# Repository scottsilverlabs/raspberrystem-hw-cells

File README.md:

raspberrystem-hw-cells
======================

raspberrySTEM(TM) Cells hardware schematics and related documents

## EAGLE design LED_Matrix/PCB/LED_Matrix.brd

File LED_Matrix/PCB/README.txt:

File List

gerbers/*.GBL       Bottom Copper
gerbers/*.GBO       Bottom Silkscreen
gerbers/*.GBS       Bottom Soldermask
gerbers/*.GTL       Top Copper
gerbers/*.GTO       Top Silkscreen
gerbers/*.GTP       Top Paste
gerbers/*.GTS       Top Soldermask
gerbers/*.TXT       Drill File
gerbers/*.dri       Drill Station Info File
gerbers/*.gpi       Photoplotter Info File   
*.brd               EagleCAD Board File
*.lbr               EagleCAD Library File
*.sch               EagleCAD Schematic File
*_BOM.xls           BOM
README.txt          This file
*.jpg               Reference images

Notes:

- Gerber Files Generated from EagleCAD 7.1 CAM Processor using sfe-gerb274x.cam
  from www.sparkfun.com
- All parts and assembly should be Lead-Free RoHS compliant

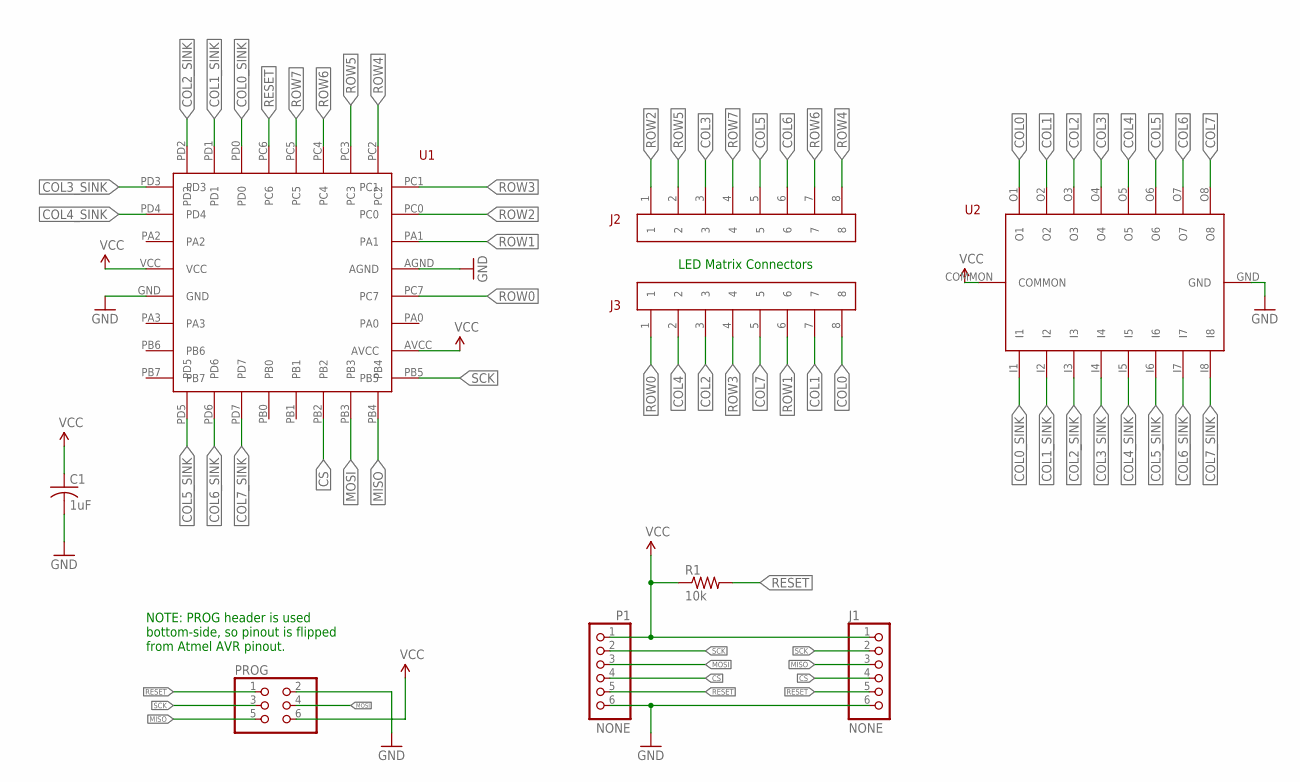
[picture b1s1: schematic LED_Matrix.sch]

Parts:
C1: 1uF; C0603
J1: NONE; 1X06
J2, J3: HEADER-1X8
P1: NONE; 1X06
PROG: NONE; 2X03
R1: 10k; R0603
U1: ATTINY48
U2: ULN2803AFWG

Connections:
COL0: J3.8, U2.O1
COL0_SINK: U1.PD0, U2.I1
COL1: J3.7, U2.O2
COL1_SINK: U1.PD1, U2.I2
COL2: J3.3, U2.O3
COL2_SINK: U1.PD2, U2.I3
COL3: J2.3, U2.O4
COL3_SINK: U1.PD3, U2.I4
COL4: J3.2, U2.O5
COL4_SINK: U1.PD4, U2.I5
COL5: J2.5, U2.O6
COL5_SINK: U1.PD5, U2.I6
COL6: J2.6, U2.O7
COL6_SINK: U1.PD6, U2.I7
COL7: J3.5, U2.O8
COL7_SINK: U1.PD7, U2.I8
CS: J1.4, P1.4, U1.PB2
GND: C1.2, J1.6, P1.6, PROG.2, U1.AGND, U1.GND, U2.GND
MISO: J1.3, PROG.5, U1.PB4
MOSI: P1.3, PROG.4, U1.PB3
RESET: J1.5, P1.5, PROG.1, R1.2, U1.PC6
ROW0: J3.1, U1.PC7
ROW1: J3.6, U1.PA1
ROW2: J2.1, U1.PC0
ROW3: J3.4, U1.PC1
ROW4: J2.8, U1.PC2
ROW5: J2.2, U1.PC3
ROW6: J2.7, U1.PC4
ROW7: J2.4, U1.PC5
SCK: J1.2, P1.2, PROG.3, U1.PB5
VCC: C1.1, J1.1, P1.1, PROG.6, R1.1, U1.AVCC, U1.VCC, U2.COMMON

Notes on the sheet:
NOTE: PROG header is used bottom-side, so pinout is flipped from Atmel AVR pinout.
LED Matrix Connectors

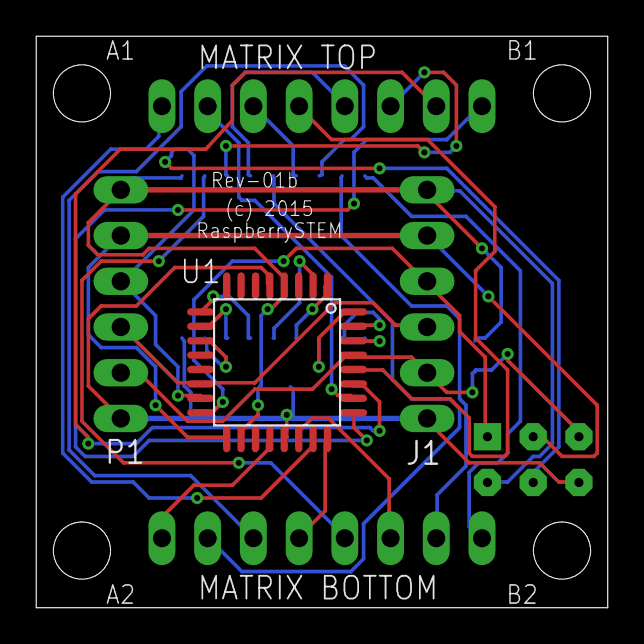
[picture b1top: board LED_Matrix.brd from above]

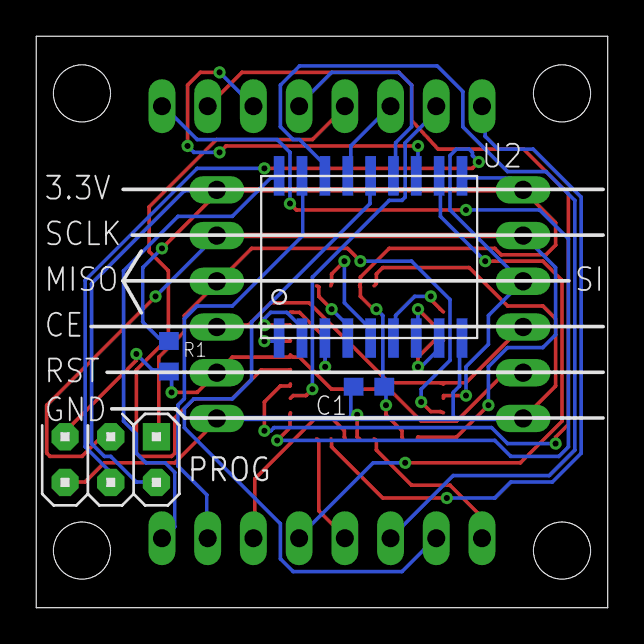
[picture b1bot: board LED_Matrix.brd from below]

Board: 2 copper layers, 31.8 x 31.8 mm, 9 parts (3 on the bottom side), 31 nets.

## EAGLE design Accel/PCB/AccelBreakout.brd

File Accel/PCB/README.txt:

File List

gerbers/*.GBL       Bottom Copper
gerbers/*.GBO       Bottom Silkscreen
gerbers/*.GBS       Bottom Soldermask
gerbers/*.GTL       Top Copper
gerbers/*.GTO       Top Silkscreen
gerbers/*.GTP       Top Paste
gerbers/*.GTS       Top Soldermask
gerbers/*.TXT       Drill File
gerbers/*.dri       Drill Station Info File
gerbers/*.gpi       Photoplotter Info File   
*.brd               EagleCAD Board File
*.lbr               EagleCAD Library File
*.sch               EagleCAD Schematic File
*_BOM.xls           BOM
README.txt          This file
*.jpg               Reference images

Notes:

- Gerber Files Generated from EagleCAD 7.1 CAM Processor using sfe-gerb274x.cam
  from www.sparkfun.com
- All parts and assembly should be Lead-Free RoHS compliant
- Refer to the JPG images for through-hole part orientation.

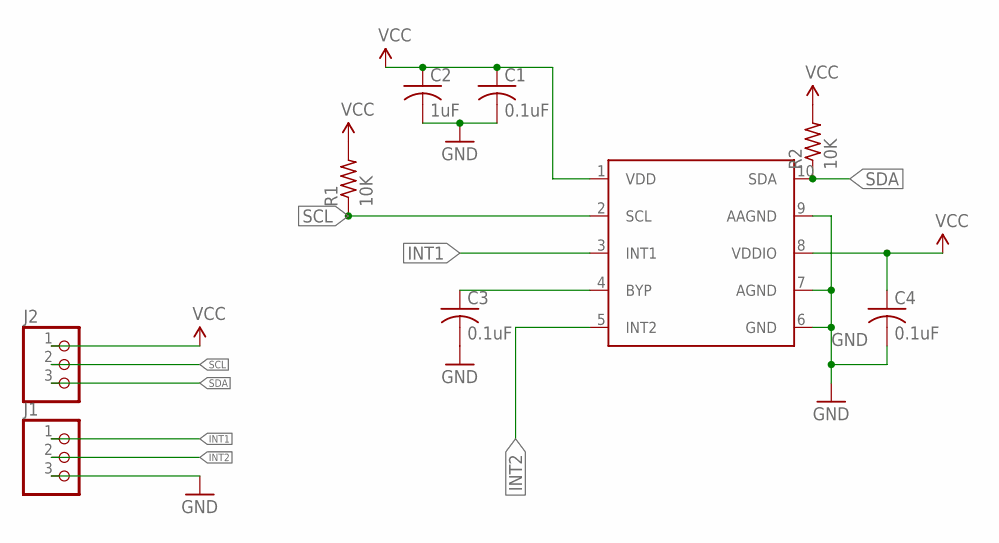
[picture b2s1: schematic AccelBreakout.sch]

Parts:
C1, C3, C4: 0.1uF; C0603
C2: 1uF; C0603
J1, J2: PINHD-1X3; 1X03
R1, R2: 10K; R0603
U1: MMA8653FCR1

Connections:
GND: C1.2, C2.2, C3.2, C4.2, J1.3, U1.6 (GND), U1.7 (AGND), U1.9 (AAGND)
INT1: J1.1, U1.3 (INT1)
INT2: J1.2, U1.5 (INT2)
unnamed: C3.1, U1.4 (BYP)
SCL: J2.2, R1.1, U1.2 (SCL)
SDA: J2.3, R2.1, U1.10 (SDA)
VCC: C1.1, C2.1, C4.1, J2.1, R1.2, R2.2, U1.1 (VDD), U1.8 (VDDIO)

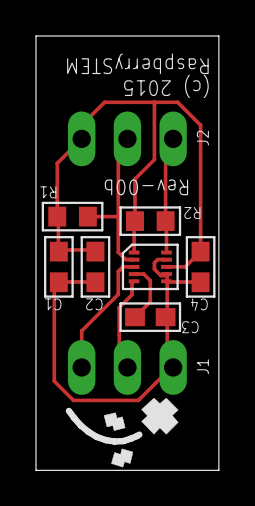
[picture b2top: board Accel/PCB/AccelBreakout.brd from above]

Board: 2 copper layers, 10.2 x 24.1 mm, 9 parts (0 on the bottom side), 7 nets.

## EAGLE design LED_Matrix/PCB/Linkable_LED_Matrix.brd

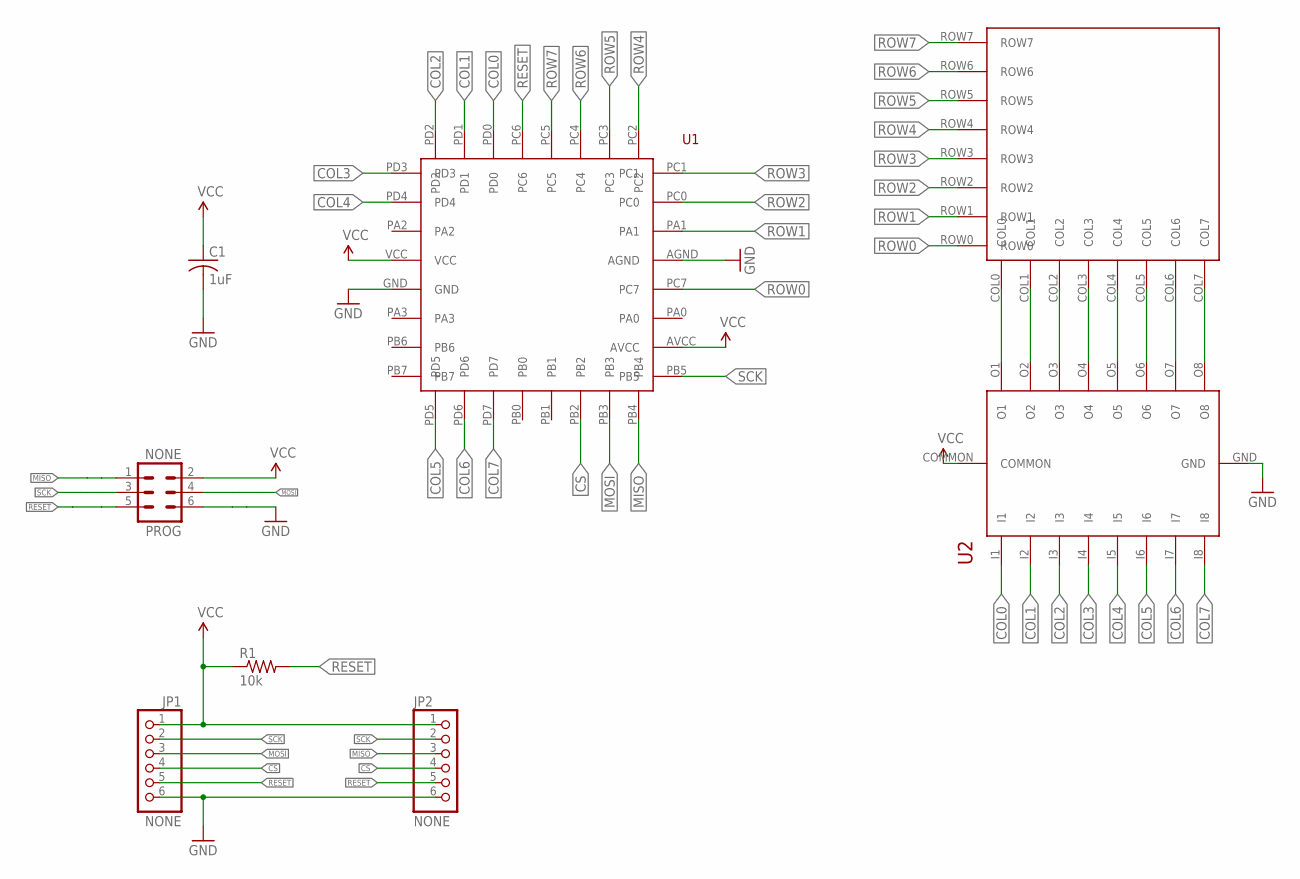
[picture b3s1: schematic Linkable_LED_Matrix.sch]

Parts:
C1: 1uF; C0603
JP1, JP2: NONE; 1X06
LEDMATRIX: 8X8_LED_MATRIX
PROG: NONE; MA03-2
R1: 10k; R0603
U1: ATTINY48
U2: ULN2803AFWG

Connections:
COL0: U1.PD0, U2.I1
COL1: U1.PD1, U2.I2
COL2: U1.PD2, U2.I3
COL3: U1.PD3, U2.I4
COL4: U1.PD4, U2.I5
COL5: U1.PD5, U2.I6
COL6: U1.PD6, U2.I7
COL7: U1.PD7, U2.I8
CS: JP1.4, JP2.4, U1.PB2
GND: C1.2, JP1.6, JP2.6, PROG.6, U1.AGND, U1.GND, U2.GND
MISO: JP2.3, PROG.1, U1.PB4
MOSI: JP1.3, PROG.4, U1.PB3
unnamed: LEDMATRIX.COL0, U2.O1
unnamed: LEDMATRIX.COL1, U2.O2
unnamed: LEDMATRIX.COL2, U2.O3
unnamed: LEDMATRIX.COL3, U2.O4
unnamed: LEDMATRIX.COL4, U2.O5
unnamed: LEDMATRIX.COL5, U2.O6
unnamed: LEDMATRIX.COL6, U2.O7
unnamed: LEDMATRIX.COL7, U2.O8
RESET: JP1.5, JP2.5, PROG.5, R1.2, U1.PC6
ROW0: LEDMATRIX.ROW0, U1.PC7
ROW1: LEDMATRIX.ROW1, U1.PA1
ROW2: LEDMATRIX.ROW2, U1.PC0
ROW3: LEDMATRIX.ROW3, U1.PC1
ROW4: LEDMATRIX.ROW4, U1.PC2
ROW5: LEDMATRIX.ROW5, U1.PC3
ROW6: LEDMATRIX.ROW6, U1.PC4
ROW7: LEDMATRIX.ROW7, U1.PC5
SCK: JP1.2, JP2.2, PROG.3, U1.PB5
VCC: C1.1, JP1.1, JP2.1, PROG.2, R1.1, U1.AVCC, U1.VCC, U2.COMMON

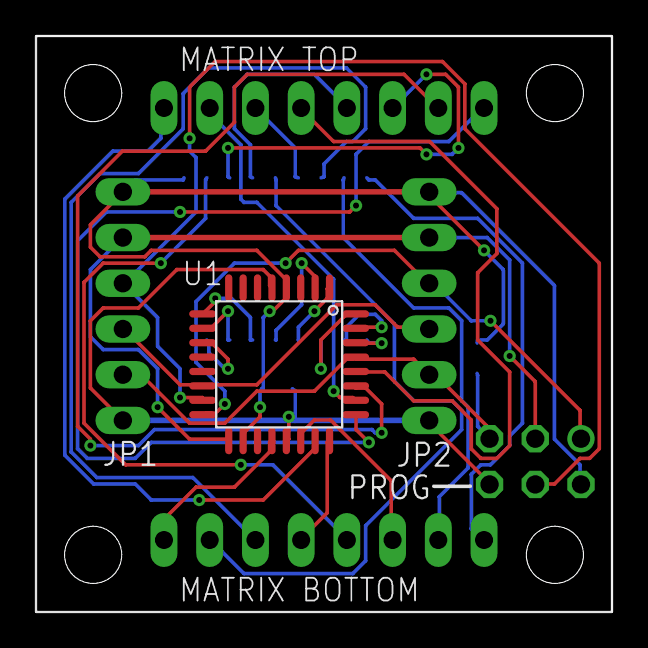
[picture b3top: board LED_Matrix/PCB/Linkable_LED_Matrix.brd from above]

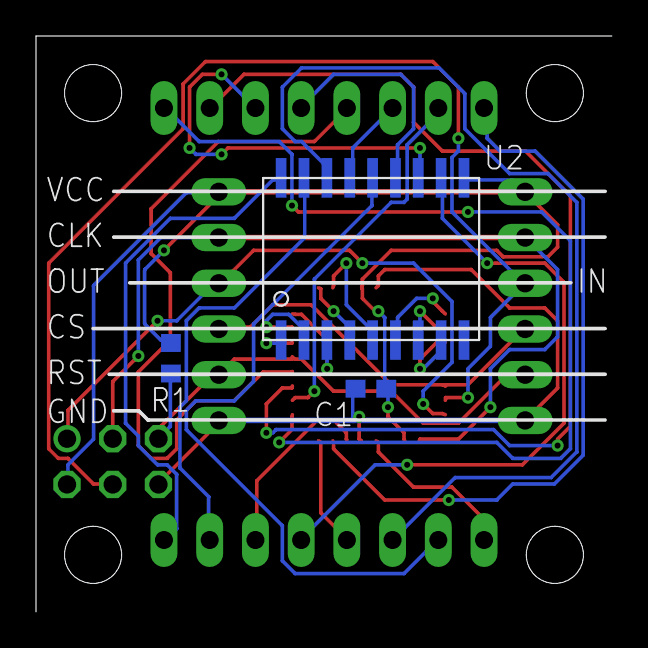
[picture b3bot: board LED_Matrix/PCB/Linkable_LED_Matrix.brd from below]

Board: 2 copper layers, 32.0 x 32.0 mm, 8 parts (3 on the bottom side), 31 nets.

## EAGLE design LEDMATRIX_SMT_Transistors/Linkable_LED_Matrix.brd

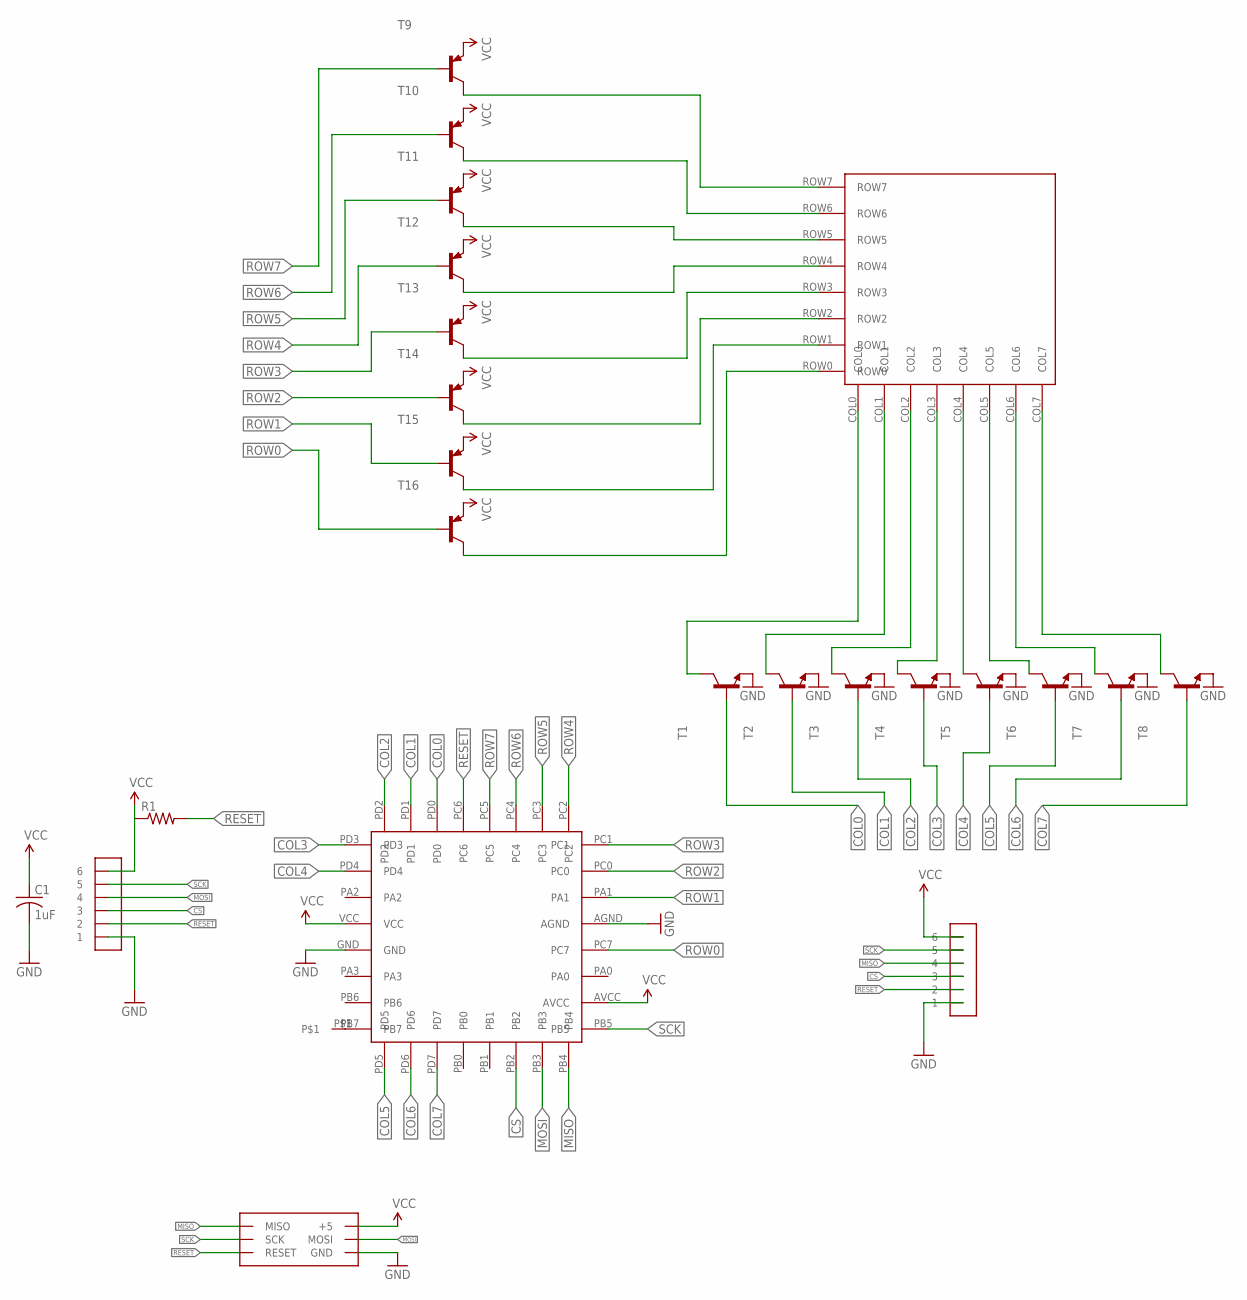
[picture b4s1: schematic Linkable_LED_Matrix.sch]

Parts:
C1: 1uF; C0603
R1: R-US_R0603; R0603
T1, T2, T3, T4, T5, T6, T7, T8: MMBT2222ALT1-NPN-SOT23-BEC; SOT23-BEC
T9, T10, T11, T12, T13, T14, T15, T16: MMBT3906LT1-PNP-SOT23-BEC; SOT23-BEC
U$1: ATTINY48
U$3: 8X8_LED_MATRIX
U$5: 1X1MM_PAD
U$6, U$7: DIP1X6MALE
U$9: DIP2X3MALE

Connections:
COL0: T1.B, U$1.PD0
COL1: T2.B, U$1.PD1
COL2: T3.B, U$1.PD2
COL3: T4.B, U$1.PD3
COL4: T5.B, U$1.PD4
COL5: T6.B, U$1.PD5
COL6: T7.B, U$1.PD6
COL7: T8.B, U$1.PD7
CS: U$1.PB2, U$6.3, U$7.3
GND: C1.2, T1.E, T2.E, T3.E, T4.E, T5.E, T6.E, T7.E, T8.E, U$1.AGND, U$1.GND, U$6.1, U$7.1, U$9.GND
MISO: U$1.PB4, U$7.4, U$9.MISO
MOSI: U$1.PB3, U$6.4, U$9.MOSI
unnamed: T1.C, U$3.COL0
unnamed: T3.C, U$3.COL2
unnamed: T4.C, U$3.COL3
unnamed: T5.C, U$3.COL4
unnamed: T6.C, U$3.COL5
unnamed: T7.C, U$3.COL6
unnamed: T8.C, U$3.COL7
unnamed: U$1.PB7, U$5.P$1
unnamed: T2.C, U$3.COL1
unnamed: T9.C, U$3.ROW7
unnamed: T10.C, U$3.ROW6
unnamed: T11.C, U$3.ROW5
unnamed: T12.C, U$3.ROW4
unnamed: T13.C, U$3.ROW3
unnamed: T14.C, U$3.ROW2
unnamed: T15.C, U$3.ROW1
unnamed: T16.C, U$3.ROW0
RESET: R1.2, U$1.PC6, U$6.2, U$7.2, U$9.RESET
ROW0: T16.B, U$1.PC7
ROW1: T15.B, U$1.PA1
ROW2: T14.B, U$1.PC0
ROW3: T13.B, U$1.PC1
ROW4: T12.B, U$1.PC2
ROW5: T11.B, U$1.PC3
ROW6: T10.B, U$1.PC4
ROW7: T9.B, U$1.PC5
SCK: U$1.PB5, U$6.5, U$7.5, U$9.SCK
VCC: C1.1, R1.1, T9.E, T10.E, T11.E, T12.E, T13.E, T14.E, T15.E, T16.E, U$1.AVCC, U$1.VCC, U$6.6, U$7.6, U$9.5V (+5)

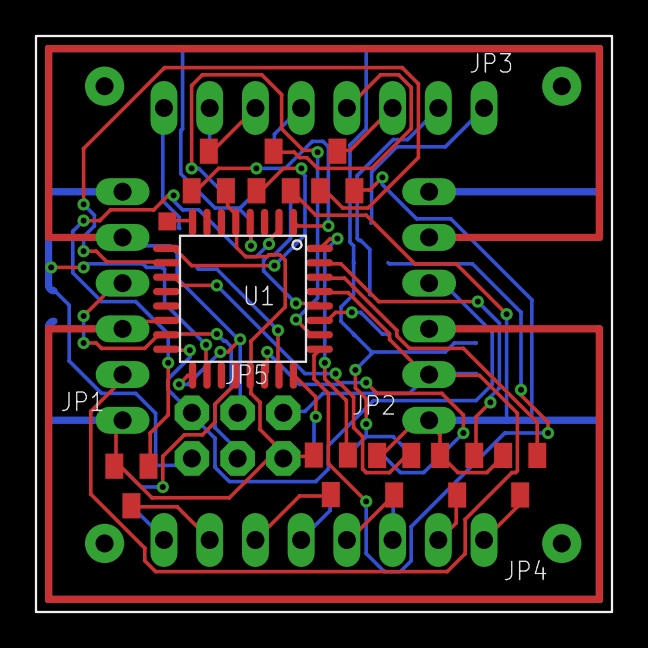
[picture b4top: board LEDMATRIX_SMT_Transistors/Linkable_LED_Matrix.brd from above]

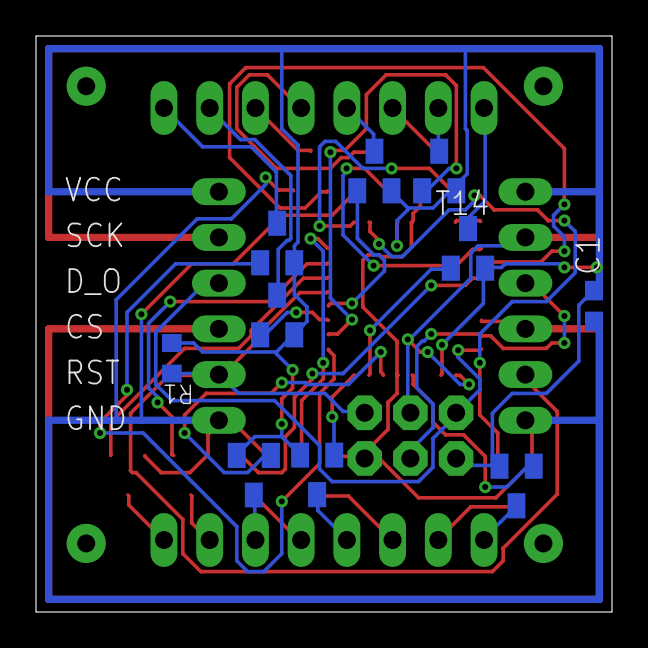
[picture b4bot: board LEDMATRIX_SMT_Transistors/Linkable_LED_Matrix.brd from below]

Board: 2 copper layers, 32.0 x 32.0 mm, 24 parts (11 on the bottom side), 40 nets.

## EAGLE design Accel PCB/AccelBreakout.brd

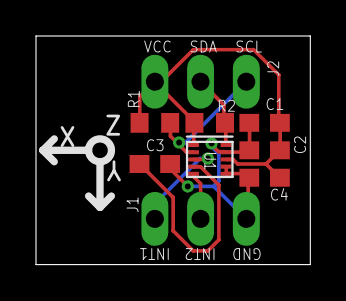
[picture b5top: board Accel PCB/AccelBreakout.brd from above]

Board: 2 copper layers, 15.2 x 12.7 mm, 10 parts (0 on the bottom side), 7 nets.

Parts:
C1, C3, C4: 0.1uF; C0603
C2: 1uF; C0603
R1, R2: 10K; R0603
U$2: ACCELDIR
U$3, U$4: DIP1X3MALE
U$23: MMA8653FCR1

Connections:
GND: C1.2, C2.2, C3.2, C4.2, U$4.P$3, U$23.6, U$23.7, U$23.9
INT1: U$4.P$1, U$23.3
INT2: U$4.P$2, U$23.5
unnamed: C3.1, U$23.4
SCL: R1.1, U$3.P$3, U$23.2
SDA: R2.1, U$3.P$2, U$23.10
VCC: C1.1, C2.1, C4.1, R1.2, R2.2, U$3.P$1, U$23.1, U$23.8

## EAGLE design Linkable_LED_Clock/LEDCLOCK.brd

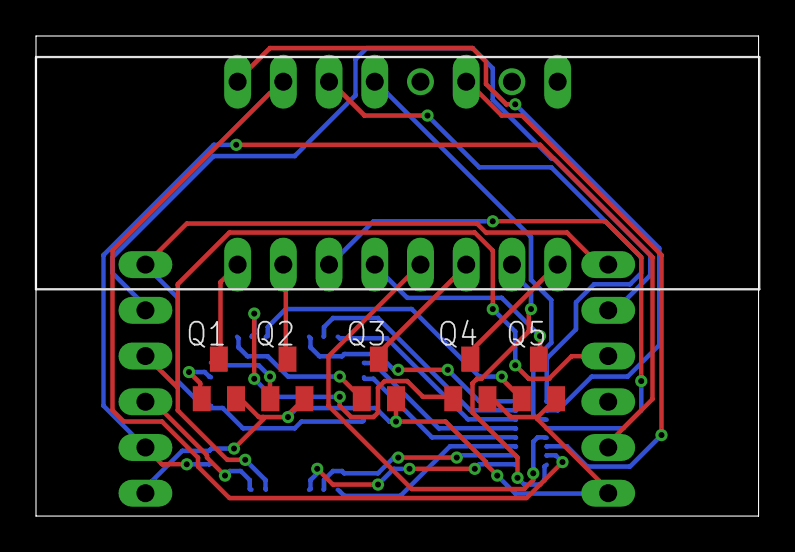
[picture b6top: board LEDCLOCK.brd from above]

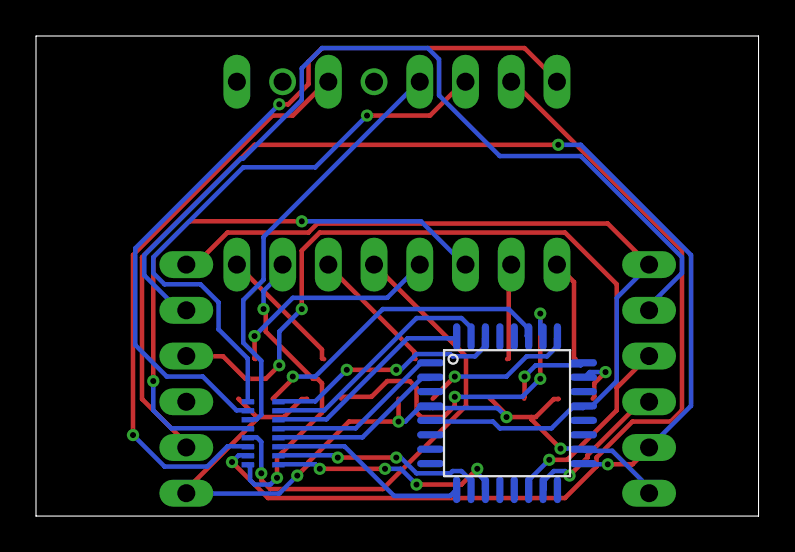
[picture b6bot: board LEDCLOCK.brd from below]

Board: 2 copper layers, 40.1 x 26.7 mm, 10 parts (2 on the bottom side), 32 nets.

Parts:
Q1, Q2, Q3, Q4, Q5: MMBT2907ALT1SMD; SOT23-BEC
U$1: LEDCLOCK
U$2, U$4: DIP1X6MALE
U$3: RES_ARRAY
U$5: ATTINY48

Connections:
A: U$3.R8, U$5.PD0
B: U$3.R7, U$5.PD1
C: U$3.R6, U$5.PD2
CLK: U$2.2, U$4.2, U$5.PB5
D: U$3.R5, U$5.PD3
DIGIT1: Q1.B, U$5.PC0
DIGIT2: Q2.B, U$5.PC1
DIGIT3: Q3.B, U$5.PC2
DIGIT4: Q4.B, U$5.PC3
DP: U$3.R1, U$5.PD7
E: U$3.R4, U$5.PD4
F: U$3.R3, U$5.PD5
G: U$3.R2, U$5.PD6
GND: U$2.6, U$4.6, U$5.AGND, U$5.GND
MOD: Q5.B, U$5.PC4
MOSI: U$2.3, U$5.PB3
unnamed: Q1.C, U$1.1
unnamed: Q2.C, U$1.2
unnamed: Q3.C, U$1.6
unnamed: Q4.C, U$1.8
unnamed: Q5.C, U$1.4
RA: U$1.14, U$3.8R
RB: U$1.16, U$3.7R
RC: U$1.13, U$3.6R
RD: U$1.3, U$3.5R
RDP: U$1.7, U$3.1R
RE: U$1.5, U$3.4R
RESET: U$2.5, U$4.5
RF: U$1.11, U$3.3R
RG: U$1.15, U$3.2R
SS: U$2.4, U$4.4, U$5.PB2
VCC: Q1.E, Q2.E, Q3.E, Q4.E, Q5.E, U$2.1, U$4.1, U$5.AVCC, U$5.VCC

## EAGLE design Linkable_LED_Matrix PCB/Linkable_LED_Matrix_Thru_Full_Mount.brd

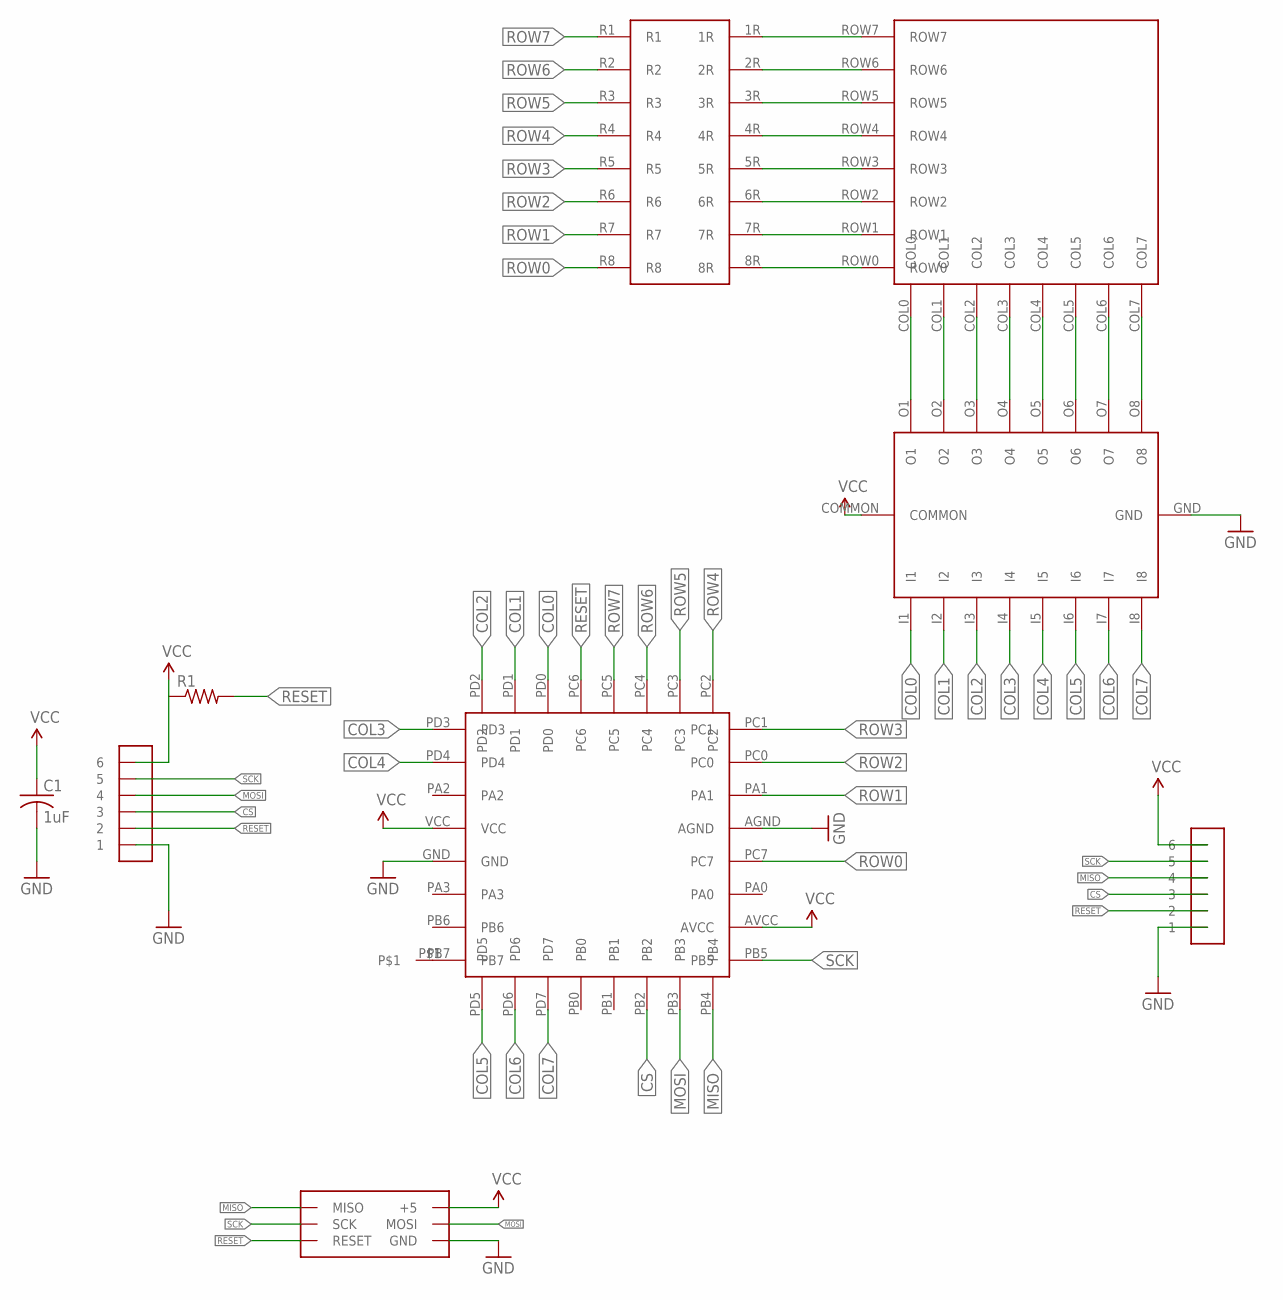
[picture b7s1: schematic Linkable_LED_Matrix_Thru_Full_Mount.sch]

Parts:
C1: 1uF; C0603
R1: R-US_R0603; R0603
U$1: ATTINY48
U$2: ULN2803AFWG
U$3: 8X8_LED_MATRIX
U$4: RES_ARRAY
U$5: 1X1MM_PAD
U$6, U$7: DIP1X6MALE
U$9: DIP2X3MALE

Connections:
COL0: U$1.PD0, U$2.I1
COL1: U$1.PD1, U$2.I2
COL2: U$1.PD2, U$2.I3
COL3: U$1.PD3, U$2.I4
COL4: U$1.PD4, U$2.I5
COL5: U$1.PD5, U$2.I6
COL6: U$1.PD6, U$2.I7
COL7: U$1.PD7, U$2.I8
CS: U$1.PB2, U$6.3, U$7.3
GND: C1.2, U$1.AGND, U$1.GND, U$2.GND, U$6.1, U$7.1, U$9.GND
MISO: U$1.PB4, U$7.4, U$9.MISO
MOSI: U$1.PB3, U$6.4, U$9.MOSI
unnamed: U$2.O1, U$3.COL0
unnamed: U$2.O2, U$3.COL1
unnamed: U$2.O3, U$3.COL2
unnamed: U$2.O4, U$3.COL3
unnamed: U$2.O5, U$3.COL4
unnamed: U$2.O6, U$3.COL5
unnamed: U$2.O7, U$3.COL6
unnamed: U$2.O8, U$3.COL7
unnamed: U$1.PB7, U$5.P$1
unnamed: U$3.ROW7, U$4.1R
unnamed: U$3.ROW6, U$4.2R
unnamed: U$3.ROW5, U$4.3R
unnamed: U$3.ROW4, U$4.4R
unnamed: U$3.ROW3, U$4.5R
unnamed: U$3.ROW2, U$4.6R
unnamed: U$3.ROW1, U$4.7R
unnamed: U$3.ROW0, U$4.8R
RESET: R1.2, U$1.PC6, U$6.2, U$7.2, U$9.RESET
ROW0: U$1.PC7, U$4.R8
ROW1: U$1.PA1, U$4.R7
ROW2: U$1.PC0, U$4.R6
ROW3: U$1.PC1, U$4.R5
ROW4: U$1.PC2, U$4.R4
ROW5: U$1.PC3, U$4.R3
ROW6: U$1.PC4, U$4.R2
ROW7: U$1.PC5, U$4.R1
SCK: U$1.PB5, U$6.5, U$7.5, U$9.SCK
VCC: C1.1, R1.1, U$1.AVCC, U$1.VCC, U$2.COMMON, U$6.6, U$7.6, U$9.5V (+5)

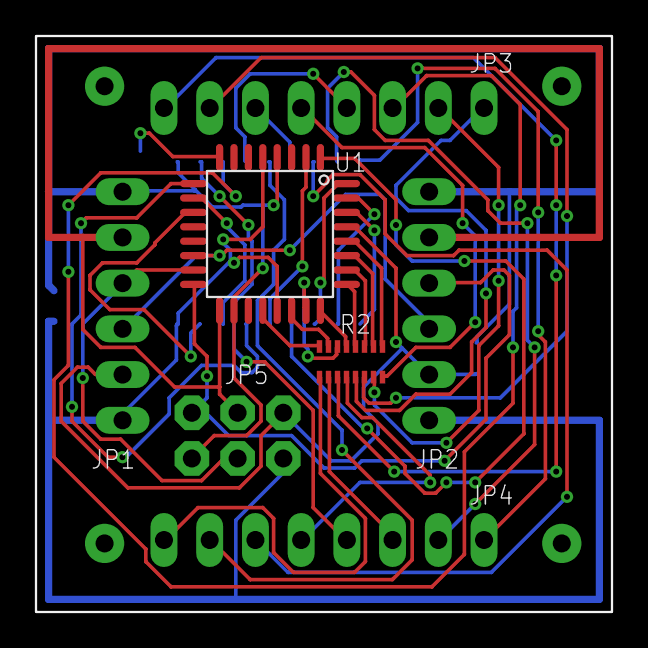
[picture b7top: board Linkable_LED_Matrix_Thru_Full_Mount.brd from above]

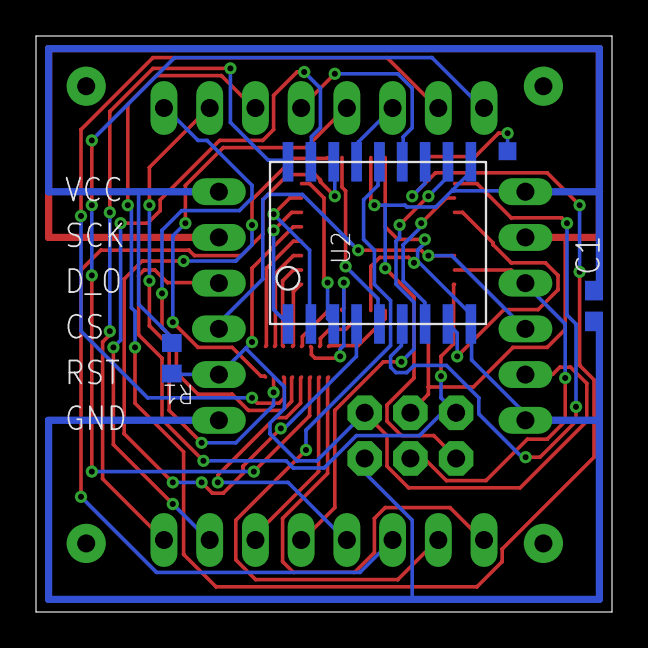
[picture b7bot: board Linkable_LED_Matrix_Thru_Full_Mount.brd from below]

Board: 2 copper layers, 32.0 x 32.0 mm, 10 parts (5 on the bottom side), 40 nets.

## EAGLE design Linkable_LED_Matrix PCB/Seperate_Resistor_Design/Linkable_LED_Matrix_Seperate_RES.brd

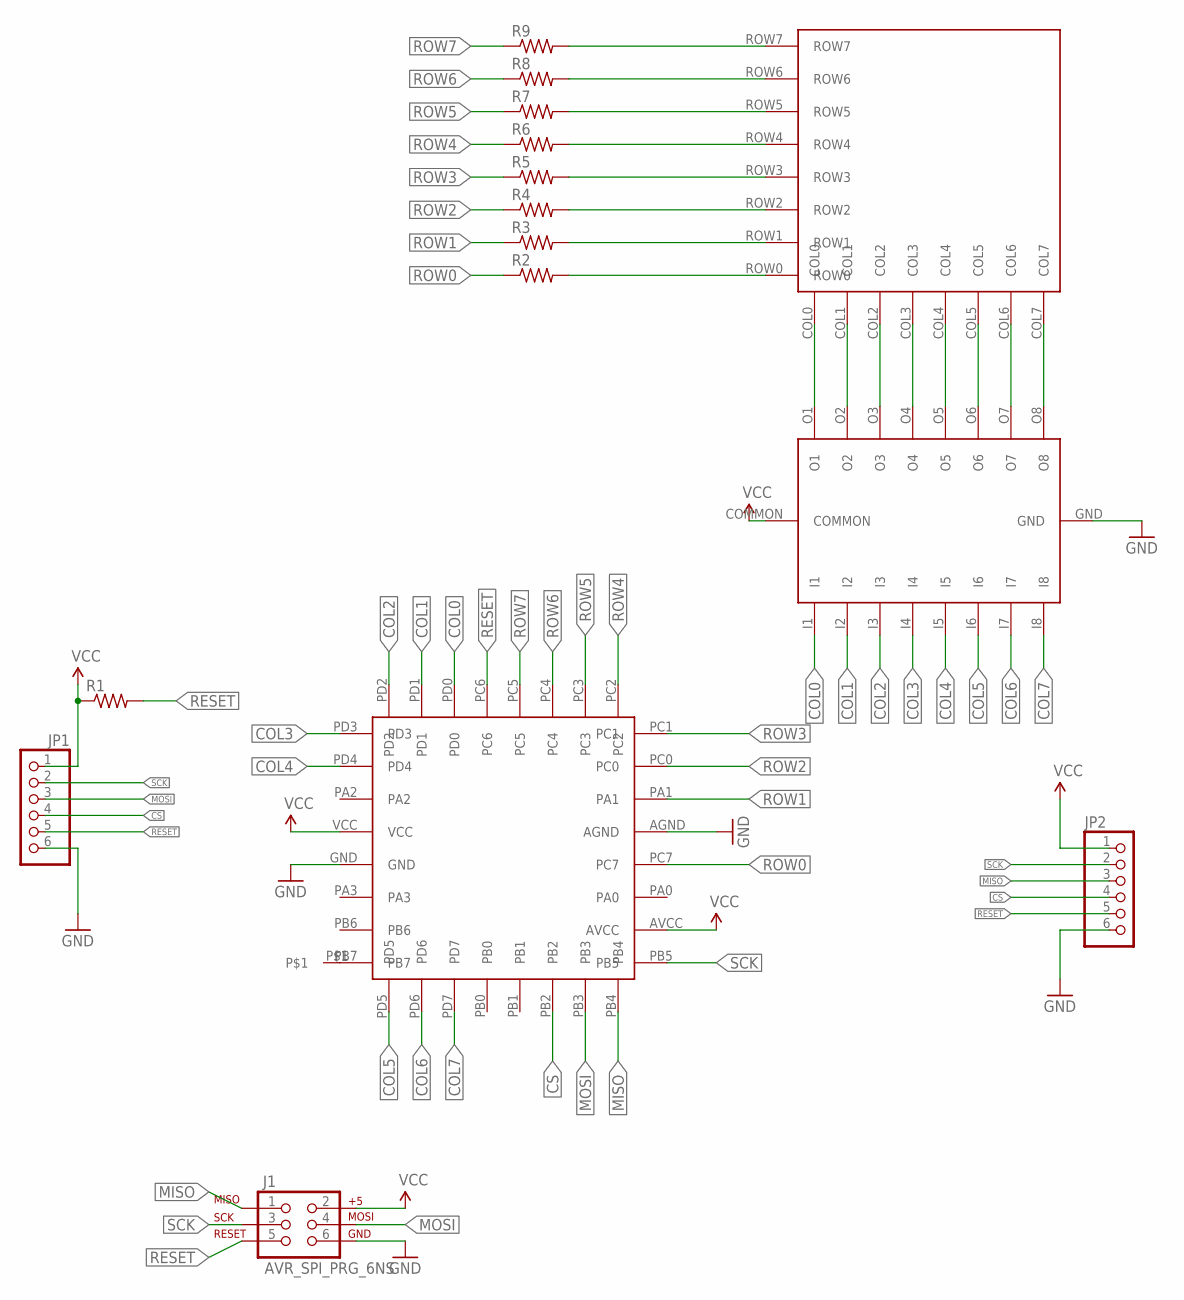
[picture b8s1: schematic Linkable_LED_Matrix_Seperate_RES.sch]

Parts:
J1: AVR_SPI_PRG_6NS; 2X3-NS
JP1, JP2: PINHD-1X6; 1X06
R1, R2, R3, R4, R5, R6, R7, R8, R9: R-US_R0603; R0603
U$1: ATTINY48
U$2: ULN2803AFWG
U$3: 8X8_LED_MATRIX
U$4: 1X1MM_PAD

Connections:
COL0: U$1.PD0, U$2.I1
COL1: U$1.PD1, U$2.I2
COL2: U$1.PD2, U$2.I3
COL3: U$1.PD3, U$2.I4
COL4: U$1.PD4, U$2.I5
COL5: U$1.PD5, U$2.I6
COL6: U$1.PD6, U$2.I7
COL7: U$1.PD7, U$2.I8
CS: JP1.4, JP2.4, U$1.PB2
GND: J1.6, JP1.6, JP2.6, U$1.AGND, U$1.GND, U$2.GND
MISO: J1.1, JP2.3, U$1.PB4
MOSI: J1.4, JP1.3, U$1.PB3
unnamed: U$2.O1, U$3.COL0
unnamed: U$2.O2, U$3.COL1
unnamed: U$2.O3, U$3.COL2
unnamed: U$2.O4, U$3.COL3
unnamed: U$2.O5, U$3.COL4
unnamed: U$2.O6, U$3.COL5
unnamed: U$2.O7, U$3.COL6
unnamed: U$2.O8, U$3.COL7
unnamed: U$1.PB7, U$4.P$1
unnamed: R9.2, U$3.ROW7
unnamed: R8.2, U$3.ROW6
unnamed: R7.2, U$3.ROW5
unnamed: R6.2, U$3.ROW4
unnamed: R5.2, U$3.ROW3
unnamed: R4.2, U$3.ROW2
unnamed: R3.2, U$3.ROW1
unnamed: R2.2, U$3.ROW0
RESET: J1.5, JP1.5, JP2.5, R1.2, U$1.PC6
ROW0: R2.1, U$1.PC7
ROW1: R3.1, U$1.PA1
ROW2: R4.1, U$1.PC0
ROW3: R5.1, U$1.PC1
ROW4: R6.1, U$1.PC2
ROW5: R7.1, U$1.PC3
ROW6: R8.1, U$1.PC4
ROW7: R9.1, U$1.PC5
SCK: J1.3, JP1.2, JP2.2, U$1.PB5
VCC: J1.2, JP1.1, JP2.1, R1.1, U$1.AVCC, U$1.VCC, U$2.COMMON

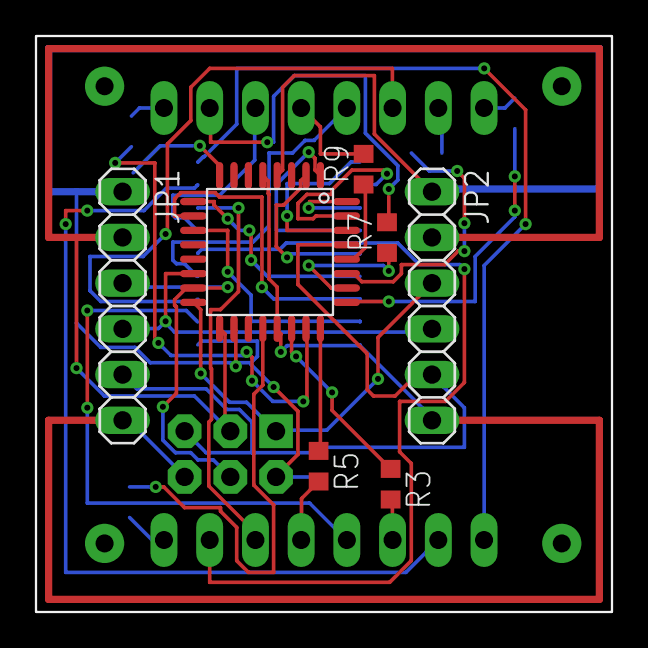
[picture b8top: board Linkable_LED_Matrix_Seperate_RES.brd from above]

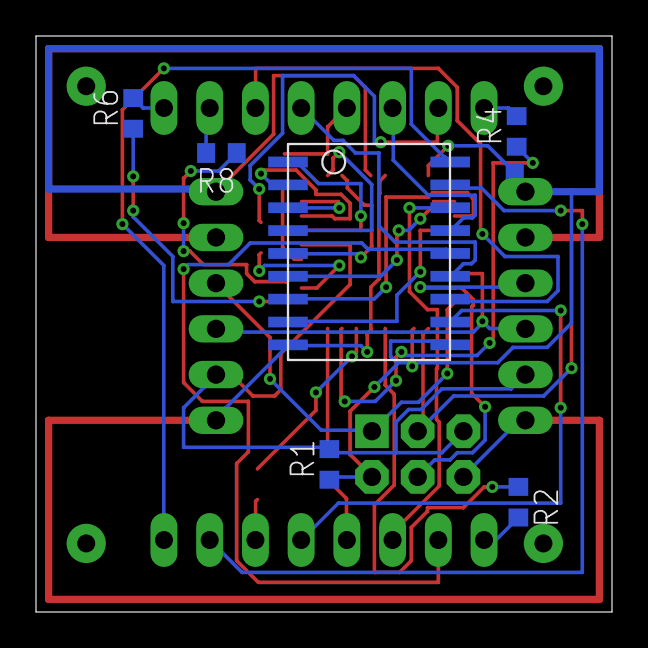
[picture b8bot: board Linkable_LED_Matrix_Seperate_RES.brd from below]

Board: 2 copper layers, 32.0 x 32.0 mm, 16 parts (7 on the bottom side), 40 nets.

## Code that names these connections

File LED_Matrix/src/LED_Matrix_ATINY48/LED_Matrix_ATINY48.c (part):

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// column - this makes column scanning easy.  Not so with the rows, which have
// to be mapped, and are on different ports.
#define COL_PORT PORTD
#define ROW0 (1<<PORTC7)
#define ROW1 (1<<PORTA1)
#define ROW2 (1<<PORTC0)
#define ROW3 (1<<PORTC1)
#define ROW4 (1<<PORTC2)
#define ROW5 (1<<PORTC3)
#define ROW6 (1<<PORTC4)
#define ROW7 (1<<PORTC5)

#define NUM_COLS 8
#define HALF_COLS 4
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
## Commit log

2014-06-25 Added Accelerometer and Linkable LED Matrix files
2014-06-26 Added BOM for accel dev board
2014-06-26 Minimized the Accel PCB layout
2014-07-18 Fixed silk screen and shifted JP2 very slightly
2014-07-18 Fixed silk screen and added accelerometer directions
2014-07-22 Added bypass cap and removed deprecated seperate resistor design
2014-07-22 Fixed text and arrow orientaiton for accel PCB
2014-07-24 added silk screen to linkable LED matrix board
2014-08-12 Added C1 to BOM
2014-09-19 Split 1x6 header into 2 1x3 headers 300 mils apart to fit over center bridge on breadboard
2014-09-21 Holes are now equidistant from the edges and the resistor array was removed
2014-09-26 Mounting holes are now equidistant apart, removed uneeded resistor package
2014-10-03 Added board for linkable LED Clock Cell
2014-10-03 Board now flush
2014-11-07 Added Design with Separate Transistors
2014-12-17 Rearranging file hierarchy for consistency
2014-12-17 Source from Joe's latest and greatest version
2014-12-17 reformating (dos2unix, retab)
2014-12-18 Refactored - commented, cleaned, removed potential race conditions
    Resolves issue #7 by increasing frame rate (previously frame rate was as fast
    as possible, now its configurable and currently set to 120HZ)
2014-12-18 ISR optimizations
    Faster ISR means SPI working up to 1MHz (intermittently) or 500kHz reliably. (Previous record was
    500kHz).
2014-12-19 Additional ISR optimizations for higher SPI clock speed.
    Now running at 1MHz SPI clock reliably. Tested overnight repeating
    led_matrix.init_grid() for one LED Matrix.
2014-12-19 Filename typo
2014-12-19 Initial POST (Power On Self Test)
2014-12-20 Added gradient display to POST
2014-12-20 Converted colors from linear PWM mapping to gemoetric.
    Linear colors converted directly to PWM appear too different on the low end
    (and conversely too similar on the high end). Instead, convert all colors
    to a PWM using an approximate geometric sequence of 16 values, with the
    ratio 1.32 (determined experimentally to give a max value of 63).
2014-12-22 Corrected all lingering gcc warnings.
    Some, like for memset() were broken code.
2014-12-23 led - matrix - new mounting holes, rerouted...
    Added new mounting hole strategy - holes are 0.125" unplated, and can mount
    with m2.5 screws, or plastic pressfit standoffs.
    Silikscreen cleaned up - all labels moved away from vias, and placed upright.
    Added clear labelling for all parts, and put horizontal lines across the board
    showing chaining connectivity.
    Put ATTINY's decoupling cap closer to part.
2014-12-23 cleanup to pass error checks
    Stop mask fails checks for silkscreen written on top of copper, but OshPark
    automatically trims that so I've approved it all. It would be a pain to trim
    it all, so I won't (unless we need to later).
2014-12-24 led matrix - adjust text on silkscreen
2014-12-27 accel - size, layout, labels
    Adjusted size to be 0.6" DIP spacing. Better orientation and position of all
    labels. Completely rerouted to remove all vias.
2014-12-27 accel - adjusted direction symbol, replaced parts
    Some old parts were missing from raspberrystem.lbr.
2014-12-30 accel - Resized board and swapped orientation label to bottom
2014-12-31 led matrix - Moved library parts local. Added rev and copyright.
2014-12-31 led matrix - fixed silkscreen and flipped prog header
2015-01-05 accel - Added silkscreen copyright and rev
2015-01-05 accel - Moved parts to local library (from raspberrystem.lbr)
2015-01-05 accel - Added document frame
2015-01-05 accel - Fixed coordinate silkscreen label
2015-01-22 accel - silkscreen and board size changes
    Box around R/Cs. Increased board size to fit better pin labels
2015-01-23 accel - slight adjustment to silkscreen text
2015-01-23 accel - rev 00b - Added Rstem logo
2015-01-30 led matrix - resolved SPI chaining issues
    Because store and show ping-pong shift-registers were used, the data coming out
    of the MISO for the last LED in the chain was incorrect. This is not strictly
    an issue, because its passed the end of the chain. However, this is now
    changed to a perhaps better approach using only one shift-register.
2015-02-20 led matrix - Smaller PROG header holes, minor silkscreen changes. Rev-01a.
    Smaller PROG holes allow pogo pins to work without getting stuck in the holes.
2015-02-25 matrix - Optimized rate at wihich SPI data can be received without overruns.
2015-02-25 matrix - Fixed memcpy() warnings
2015-02-25 matrix - added VERSION number display on POST. Version 1.1.
2015-02-25 matrix - Fix for suprious interrupt after POST. Version 1.2
2015-03-03 matrix - Rev-01b - Adjust size, mouting holes, split matrix connector. No routing changes.
    Dimensionsional, mounting, silkscreen and schematic changes. (actually - there
    was one very minor routing adjustment where a DRC check failed).
    Changes:
    - Board was 1260x1260mils: changed to correct 1250x1250, which is the size
    of the LED matrix.
    - Mouting holes where 1010 mils apart, and still would hit the matrix
2015-03-03 matrix - Added BOM
2015-03-03 matrix - added gerbers
    Generated via CAM Processor file sfe-gerb274x.cam from www.sparkfun.com
2015-03-19 accel - Added accel IC pin name to schematic
2015-03-19 accel - BOM
2015-03-21 led matrix - BOM - added "Thru hole" to applicable parts
2015-04-15 eagle packaging - Added Makefile with instructions
2015-04-15 pcb packaging - Added board rev to output zip file package
2015-04-15 accel packaging - Created initial accel package.
    Also, updated Makefile to include JPG images
2015-04-15 packaging - Moved packaging files into raspberrystem-hw-base repo
2015-04-15 matrix/accel - Added board fab notes images

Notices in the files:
LED_Matrix/src/LED_Matrix_ATINY48/LED_Matrix_ATINY48.c:
Copyright (c) 2014, Scott Silver Labs, LLC.
Licensed under the Apache License, Version 2.0 (the "License");
parts and their libraries:
SparkFun-Aesthetics: Licensing: Creative Commons ShareAlike 4.0 International - https://creativecommons.org/licenses/by-sa/4.0
